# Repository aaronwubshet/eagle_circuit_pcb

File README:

####################################################
#############NODE ELECTRONICS#######################
####################################################
DESCRIPTION:

NODE IS A MISSION TO SEND A NANOSAT INTO LOW EARTH ORIBIT. THESE FILES ARE PART OF THE LASER COMMUNICATION SYSTEM SELF TEST FEATURE. 
GOAL OF THE CIRUITRY IS TO ENSURE THE LASER POWER LEVEL IS NOT TOO HIGH NOR TOO LOW AT DIFFERENT POINTS OR MODULATION BEFORE 
BEING USED IN ACTUAL COMMUNICATIONS

FILES CATEGORIES:

(1) DATA SHEETS
(2) SCHEMATIC PDF
(3) EAGLE SCHEMATIC FILES
(4) EAGLE LIBRARY FILE
(5) *COMING SOON* EAGLE BOARD FILE

OVERVIEW OF CONTENTS:

LIGHT DIODE AMPLIFIER CIRCUITRY AND RELEVANT DATA SHEETS

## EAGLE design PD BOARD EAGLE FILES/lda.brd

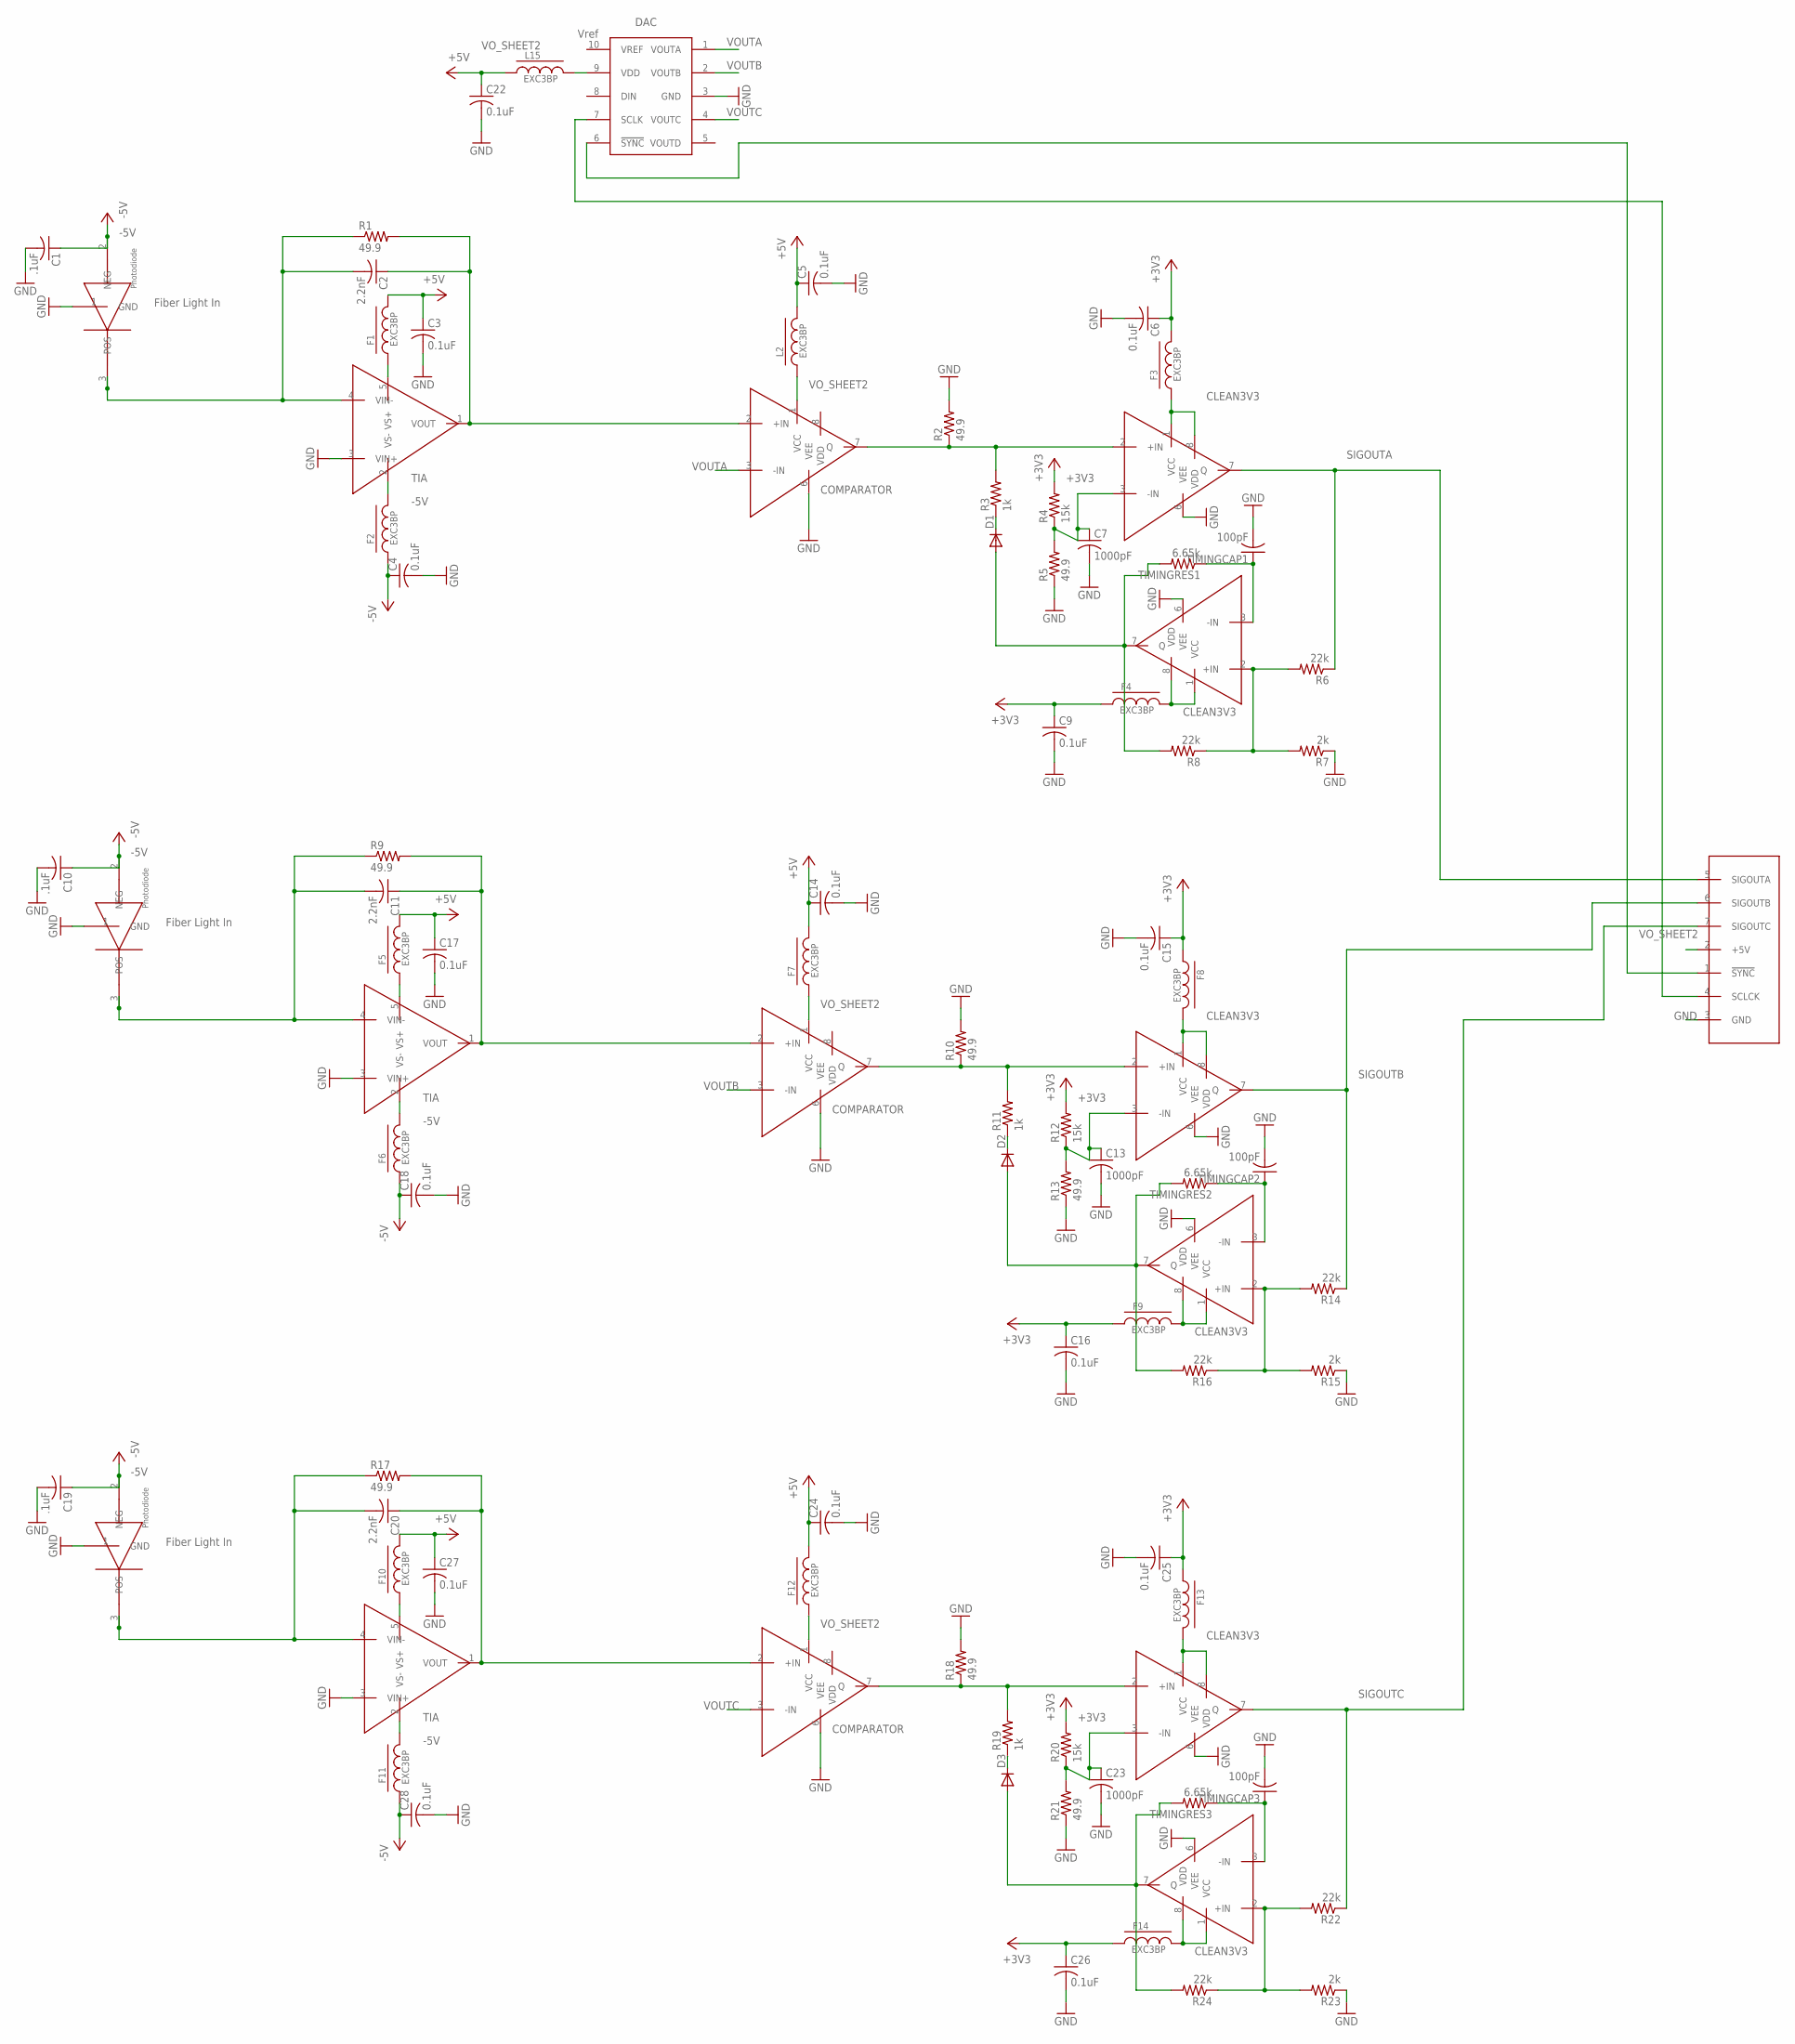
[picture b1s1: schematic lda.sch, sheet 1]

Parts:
C1, C10, C19: .1uF; C01005
C2, C11, C20: 2.2nF; C01005
C3, C4, C5, C6, C9, C14, C15, C16, C17, C18, C22, C24, C25, C26, C27, C28: 0.1uF; C01005
C7, C13, C23: 1000pF; C01005
COMPARATOR1, COMPARATOR2, COMPARATOR3, COMPARATOR4, COMPARATOR5, COMPARATOR6, COMPARATOR7, COMPARATOR8, COMPARATOR9: LTC6752DEV; MS8-MSOP
D1, D2, D3: DIODE-SOD523; SOD523
DAC: AD5624DEV; AD5624MSOP
F1, F2, F3, F4, F5, F6, F7, F8, F9, F10, F11, F12, F13, F14: EXC3BP; R01005
L2, L15: EXC3BP; R01005
PD1, PD2, PD3: EPM605DEV; PINPDBOX
R1, R2, R5, R9, R10, R13, R17, R18, R21: 49.9; R01005
R3, R11, R19: 1k; R01005
R4, R12, R20: 15k; R01005
R6, R8, R14, R16, R22, R24: 22k; R01005
R7, R15, R23: 2k; R01005
TIA1, TIA2, TIA3: OPA657DEV; OPA-SOIC
TIMINGCAP1, TIMINGCAP2, TIMINGCAP3: 100pF; C01005
TIMINGRES1, TIMINGRES2, TIMINGRES3: 6.65k; R01005
U$2: SAMTEC7PIN

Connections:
+3V3: C6.1, C9.1, C15.1, C16.1, C25.1, C26.1, F3.2, F4.1, F8.1, F9.1, F13.1, F14.1, R4.2, R12.2, R20.2; also elsewhere on the board
-5V: C1.1, C4.1, C10.1, C18.1, C19.1, C28.1, F2.1, F6.1, F11.1, PD1.2 (NEG), PD2.2 (NEG), PD3.2 (NEG); also elsewhere on the board
CLEAN3V3: COMPARATOR2.1 (VCC), COMPARATOR2.8 (VDD), COMPARATOR3.1 (VCC), COMPARATOR3.8 (VDD), COMPARATOR5.1 (VCC), COMPARATOR5.8 (VDD), COMPARATOR6.1 (VCC), COMPARATOR6.8 (VDD), COMPARATOR8.1 (VCC), COMPARATOR8.8 (VDD), COMPARATOR9.1 (VCC), COMPARATOR9.8 (VDD), F3.1, F4.2, F8.2, F9.2, F13.2, F14.2
GND: C1.2, C3.2, C4.2, C5.2, C6.2, C7.2, C9.2, C10.2, C13.2, C14.2, C15.2, C16.2, C17.2, C18.2, C19.2, C22.2, C23.2, C24.2, C25.2, C26.2, C27.2, C28.2, COMPARATOR1.6 (VEE), COMPARATOR2.6 (VEE), COMPARATOR3.6 (VEE), COMPARATOR4.6 (VEE), COMPARATOR5.6 (VEE), COMPARATOR6.6 (VEE), COMPARATOR7.6 (VEE), COMPARATOR8.6 (VEE), COMPARATOR9.6 (VEE), DAC.3 (GND), PD1.1 (GND), PD2.1 (GND), PD3.1 (GND), R2.2, R5.1, R7.1, R10.2, R13.1, R15.1, R18.2, R21.1, R23.1, TIA1.3 (VIN+), TIA2.3 (VIN+), TIA3.3 (VIN+), TIMINGCAP1.2, TIMINGCAP2.2, TIMINGCAP3.2, U$2.3 (GND); also elsewhere on the board
unnamed: F1.1, TIA1.5 (VS+)
unnamed: F2.2, TIA1.2 (VS-)
unnamed: COMPARATOR1.1 (VCC), L2.1
unnamed: C2.1, COMPARATOR1.2 (+IN), R1.2, TIA1.1 (VOUT)
unnamed: DAC.6 (!SYNC), U$2.1 (!SYNC)
unnamed: COMPARATOR1.7 (Q), COMPARATOR2.2 (+IN), R2.1, R3.2
unnamed: D1.C, R3.1
unnamed: COMPARATOR3.7 (Q), D1.A, R8.2, TIMINGRES1.2
unnamed: DAC.9 (VDD), L15.2
unnamed: COMPARATOR3.3 (-IN), TIMINGCAP1.1, TIMINGRES1.1
unnamed: C7.1, COMPARATOR2.3 (-IN), R4.1, R5.2
unnamed: COMPARATOR3.2 (+IN), R6.2, R7.2, R8.1
unnamed: C11.1, COMPARATOR4.2 (+IN), R9.2, TIA2.1 (VOUT)
unnamed: COMPARATOR4.7 (Q), COMPARATOR6.2 (+IN), R10.1, R11.2
unnamed: D2.C, R11.1
unnamed: COMPARATOR5.7 (Q), D2.A, R16.2, TIMINGRES2.2
unnamed: COMPARATOR5.3 (-IN), TIMINGCAP2.1, TIMINGRES2.1
unnamed: C13.1, COMPARATOR6.3 (-IN), R12.1, R13.2
unnamed: COMPARATOR5.2 (+IN), R14.2, R15.2, R16.1
unnamed: C11.2, PD2.3 (POS), R9.1, TIA2.4 (VIN-)
unnamed: F5.1, TIA2.5 (VS+)
unnamed: F6.2, TIA2.2 (VS-)
unnamed: COMPARATOR4.1 (VCC), F7.1
unnamed: C20.1, COMPARATOR7.2 (+IN), R17.2, TIA3.1 (VOUT)
unnamed: C2.2, PD1.3 (POS), R1.1, TIA1.4 (VIN-)
unnamed: COMPARATOR7.7 (Q), COMPARATOR9.2 (+IN), R18.1, R19.2
unnamed: D3.C, R19.1
unnamed: COMPARATOR8.7 (Q), D3.A, R24.2, TIMINGRES3.2
unnamed: COMPARATOR8.3 (-IN), TIMINGCAP3.1, TIMINGRES3.1
unnamed: C23.1, COMPARATOR9.3 (-IN), R20.1, R21.2
unnamed: COMPARATOR8.2 (+IN), R22.2, R23.2, R24.1
unnamed: C20.2, PD3.3 (POS), R17.1, TIA3.4 (VIN-)
unnamed: F10.1, TIA3.5 (VS+)
unnamed: F11.2, TIA3.2 (VS-)
unnamed: COMPARATOR7.1 (VCC), F12.1
unnamed: DAC.7 (SCLK), U$2.4 (SCLCK)
SIGOUTA: COMPARATOR2.7 (Q), R6.1, U$2.5 (SIGOUTA)
SIGOUTB: COMPARATOR6.7 (Q), R14.1, U$2.6 (SIGOUTB)
SIGOUTC: COMPARATOR9.7 (Q), R22.1, U$2.7 (SIGOUTC)
VOUTA: COMPARATOR1.3 (-IN), DAC.1 (VOUTA)
VOUTB: COMPARATOR4.3 (-IN), DAC.2 (VOUTB)
VOUTC: COMPARATOR7.3 (-IN), DAC.4 (VOUTC)
VO_SHEET2: C3.1, C5.1, C14.1, C17.1, C22.1, C24.1, C27.1, F1.2, F5.2, F7.2, F10.2, F12.2, L2.2, L15.1, U$2.2 (+5V); also elsewhere on the board

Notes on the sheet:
DAC
Vref
Fiber Light In
TIA
COMPARATOR

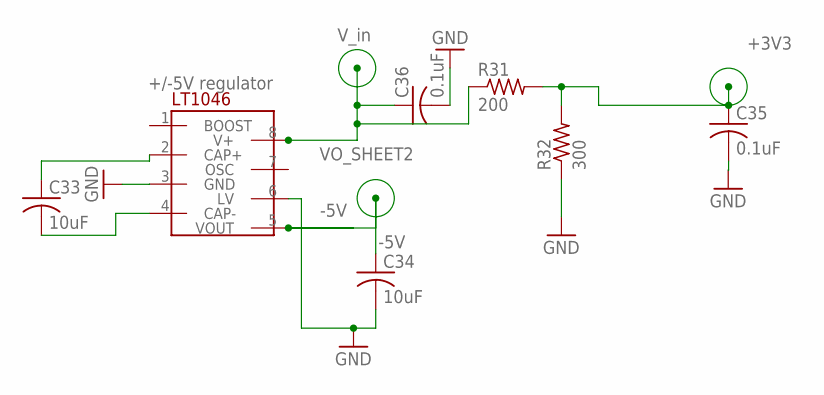
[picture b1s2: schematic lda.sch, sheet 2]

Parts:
C33, C34: 10uF; C01005
C35, C36: 0.1uF; C01005
R31: 200; R01005
R32: 300; R01005
U$1: LT1046REG; S8

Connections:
+3V3: C35.1, R31.2, R32.2; also elsewhere on the board
-5V: C34.1, U$1.5 (VOUT); also elsewhere on the board
GND: C34.2, C35.2, C36.2, R32.1, U$1.3 (GND), U$1.6 (LV); also elsewhere on the board
unnamed: C33.2, U$1.4 (CAP-)
unnamed: C33.1, U$1.2 (CAP+)
VO_SHEET2: C36.1, R31.1, U$1.8 (V+); also elsewhere on the board

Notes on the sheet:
+/-5V regulator
-5V
V_in

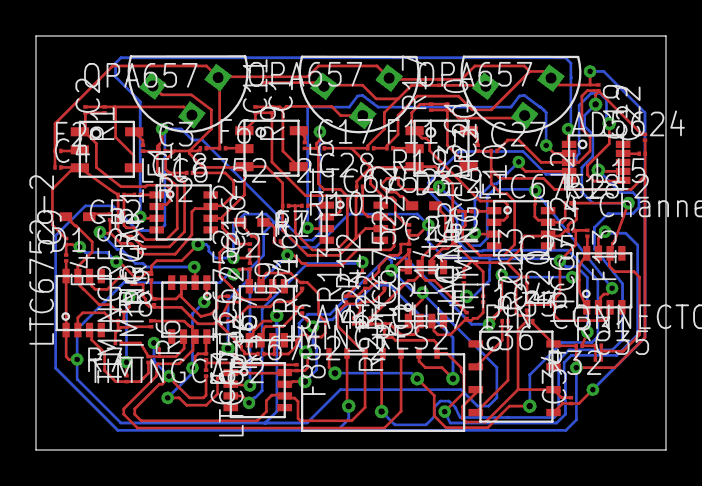
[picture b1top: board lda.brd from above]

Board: 4 copper layers, 35.0 x 23.0 mm, 98 parts (0 on the bottom side), 49 nets.

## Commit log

2017-09-23 initial commit with laser diode amplication circuitry files
